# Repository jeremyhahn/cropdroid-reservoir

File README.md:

# cropdroid-reservoir

## Support

Please consider supporting this project for ongoing success and sustainability. I'm a passionate open source contributor making a professional living creating free, secure, scalable, robust, enterprise grade, distributed systems and cloud native solutions.

I'm also available for international consulting opportunities. Please let me know how I can assist you or your organization in achieving your desired security posture and technology goals.

https://github.com/sponsors/jeremyhahn

https://www.linkedin.com/in/jeremyhahn

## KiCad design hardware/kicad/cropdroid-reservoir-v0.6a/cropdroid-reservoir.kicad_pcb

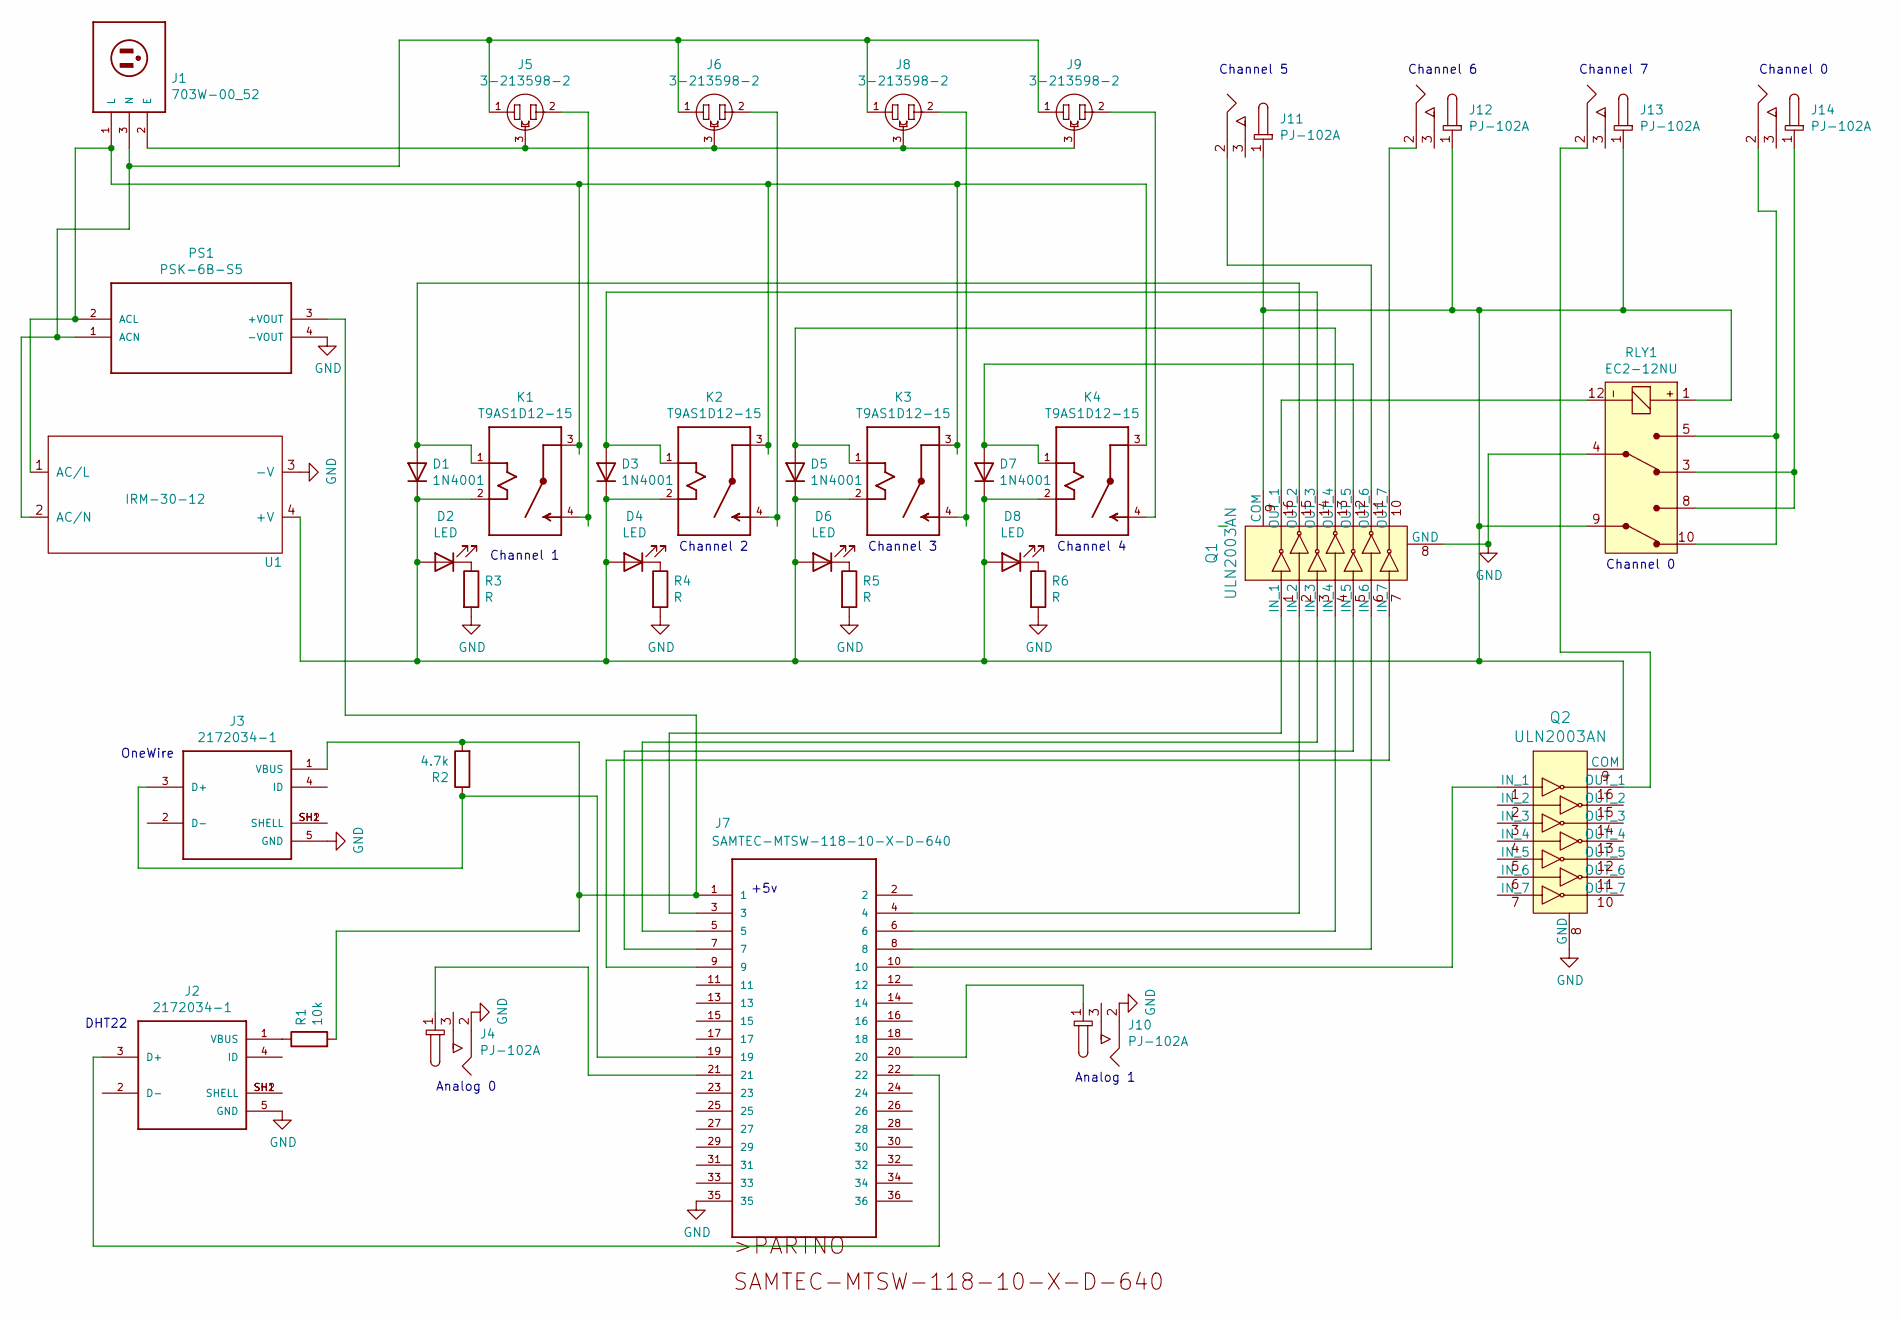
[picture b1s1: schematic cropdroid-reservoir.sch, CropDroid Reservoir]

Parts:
D1, D3, D5, D7: 1N4001; D_DO-41_SOD81_P10.16mm_Horizontal
D2, D4, D6, D8: LED; CAPPRD350W60D800H2000
J1: 703W-00_52; QUALTEK_703W-00_52
J2, J3: 2172034-1; TE_2172034-1
J4, J10, J11, J12, J13, J14: PJ-102A; Barrel_Jack_5.5mmODx2.1mmID_PJ-102A; MPN PJ-102A; Digi-Key_PN CP-102A-ND
J5, J6, J8, J9: 3-213598-2; TE_3-213598-2
J7: SAMTEC-MTSW-118-10-X-D-640
K1, K2, K3, K4: T9AS1D12-15; RELAY_T9AS1D12-15
PS1: PSK-6B-S5; CONV_PSK-6B-S5
Q1, Q2: ULN2003AN; DIP-16_W7.62mm; MPN ULN2003AN; Digi-Key_PN 296-1979-5-ND
R1: 10k; R_Axial_DIN0207_L6.3mm_D2.5mm_P10.16mm_Horizontal
R2: 4.7k; R_Axial_DIN0207_L6.3mm_D2.5mm_P10.16mm_Horizontal
R3, R4, R5, R6: R; R_Axial_DIN0207_L6.3mm_D2.5mm_P10.16mm_Horizontal
RLY1: EC2-12NU; Relay_THT_EC2; MPN EC2-12NU; Digi-Key_PN 399-11029-5-ND
U1: IRM-30-12

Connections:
GND: J2.5 (GND), J3.5 (GND), J4.2, J7.35, J10.2, PS1.4 (-VOUT), Q1.8 (GND), Q2.8 (GND), R3.2, R4.2, R5.2, R6.2, RLY1.4 (COM1), U1.3 (-V)
unnamed: D1.1 (K), D2.2 (A), D3.1 (K), D4.2 (A), D5.1 (K), D6.2 (A), D7.1 (K), D8.2 (A), J11.1, J12.1, J13.1, K1.2 (A2), K2.2 (A2), K3.2 (A2), K4.2 (A2), Q1.9 (COM), Q2.9 (COM), RLY1.1 (COIL), RLY1.9 (COM2), U1.4 (+V)
unnamed: D1.2 (A), K1.1 (A1), Q1.15 (OUT_2)
unnamed: D2.1 (K), R3.1
unnamed: D3.2 (A), K2.1 (A1), Q1.14 (OUT_3)
unnamed: D4.1 (K), R4.1
unnamed: D5.2 (A), K3.1 (A1), Q1.13 (OUT_4)
unnamed: D6.1 (K), R5.1
unnamed: D7.2 (A), K4.1 (A1), Q1.12 (OUT_5)
unnamed: D8.1 (K), R6.1
unnamed: J1.1 (L), K1.3 (C), K2.3 (C), K3.3 (C), K4.3 (C), PS1.2 (ACL), U1.1 (AC/L)
unnamed: J1.2 (E), J5.3, J6.3, J8.3, J9.3
unnamed: J1.3 (N), J5.1, J6.1, J8.1, J9.1, PS1.1 (ACN), U1.2 (AC/N)
unnamed: J2.1 (VBUS), R1.1
unnamed: J2.3 (D+), J7.22
unnamed: J2.SH1 (SHELL), J2.SH2 (SHELL)
unnamed: J3.1 (VBUS), J7.1, PS1.3 (+VOUT), R1.2, R2.2
unnamed: J3.3 (D+), J7.19, R2.1
unnamed: J3.SH1 (SHELL), J3.SH2 (SHELL)
unnamed: J4.1, J7.21
unnamed: J5.2, K1.4 (NO)
unnamed: J6.2, K2.4 (NO)
unnamed: J7.3, Q1.1 (IN_1)
unnamed: J7.4, Q1.2 (IN_2)
unnamed: J7.5, Q1.3 (IN_3)
unnamed: J7.6, Q1.4 (IN_4)
unnamed: J7.7, Q1.5 (IN_5)
unnamed: J7.8, Q1.6 (IN_6)
unnamed: J7.9, Q1.7 (IN_7)
unnamed: J7.10, Q2.1 (IN_1)
unnamed: J8.2, K3.4 (NO)
unnamed: J9.2, K4.4 (NO)
unnamed: J7.20, J10.1
unnamed: J11.2, Q1.11 (OUT_6)
unnamed: J12.2, Q1.10 (OUT_7)
unnamed: J13.2, Q2.16 (OUT_1)
unnamed: J14.1, RLY1.3 (NC1), RLY1.8 (NO2)
unnamed: J14.2, RLY1.5 (NO1), RLY1.10 (NC2)
unnamed: Q1.16 (OUT_1), RLY1.12 (COIL)

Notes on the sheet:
Channel 1
Channel 2
Channel 3
Channel 0
Channel 5
Channel 6
Channel 7
Analog 0
Analog 1
DHT22
+5v
Channel 4
OneWire

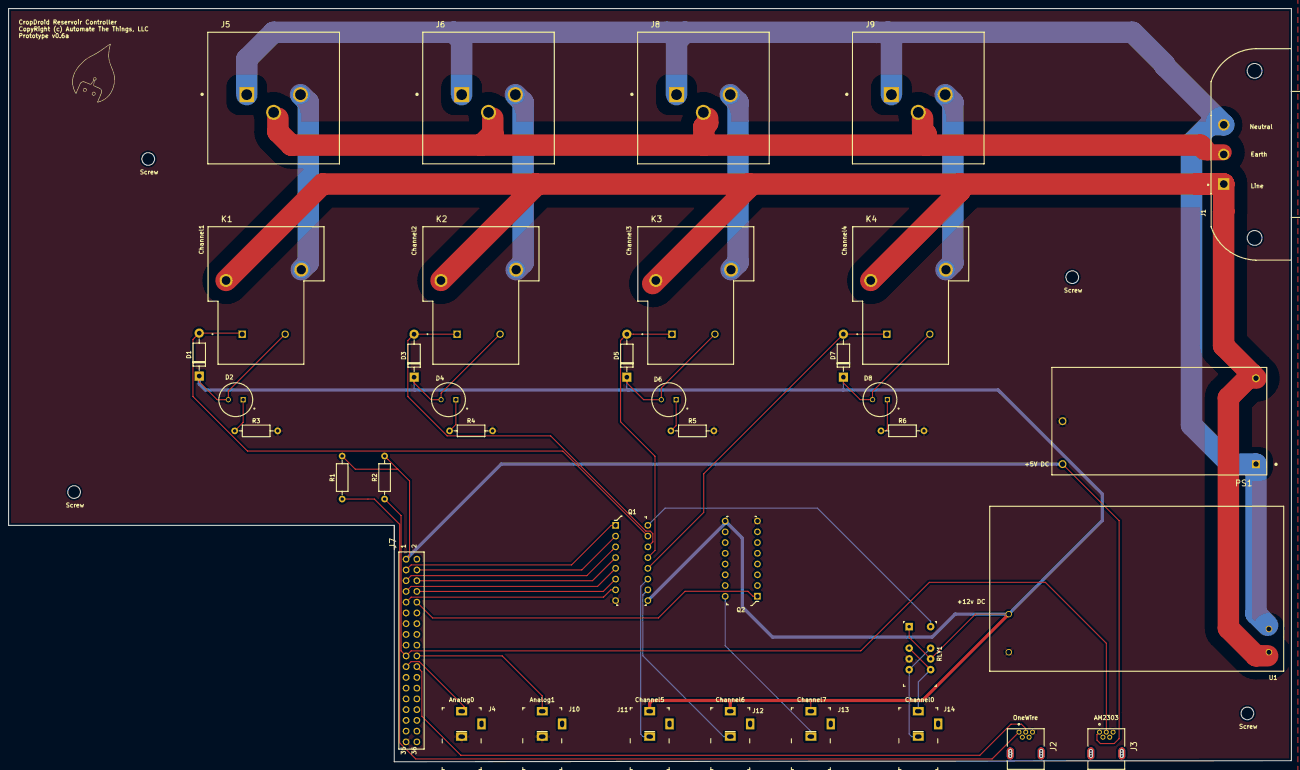
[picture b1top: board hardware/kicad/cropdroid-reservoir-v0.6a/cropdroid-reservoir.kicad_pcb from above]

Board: 2 copper layers, 303.3 x 178.1 mm, 41 parts (0 on the bottom side), 39 nets.

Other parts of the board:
Screw: Drill; Drill_Hole
Screw#2, Screw#3, Screw#4: Drill; Drill_Hole

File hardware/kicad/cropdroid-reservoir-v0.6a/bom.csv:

Reference, Quantity, Value, Footprint, Datasheet, Category, DK_Datasheet_Link, DK_Detail_Page, Description, Digi-Key_PN, Family, MPN, Manufacturer, Status, Field4, Field5, Field6
D2 D4 D6 D8 ,4,"LED","libraries:CAPPRD350W60D800H2000","~"
D3 D1 D5 D7 ,4,"1N4001","Diode_THT:D_DO-41_SOD81_P10.16mm_Horizontal","http://www.vishay.com/docs/88503/1n4001.pdf"
J1 ,1,"703W-00_52","703W-00_52:QUALTEK_703W-00_52","B","","","","","","","","","","Manufacturer Recommendations","Qualtek",""
J11 J12 J13 J14 J4 J10 ,6,"PJ-102A","digikey-footprints:Barrel_Jack_5.5mmODx2.1mmID_PJ-102A","https://www.cui.com/product/resource/digikeypdf/pj-102a.pdf","Connectors, Interconnects","https://www.cui.com/product/resource/digikeypdf/pj-102a.pdf","/product-detail/en/cui-inc/PJ-102A/CP-102A-ND/275425","CONN PWR JACK 2X5.5MM SOLDER","CP-102A-ND","Barrel - Power Connectors","PJ-102A","CUI Inc.","Active","","",""
J3 J2 ,2,"2172034-1","TE_2172034-1","Compliant","","","","","","","","","","2172034-1","https://www.te.com/usa-en/product-2172034-1.html?te_bu=Cor&t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",""
J6 J8 J5 J9 ,4,"3-213598-2","3-213598-2:TE_3-213598-2","https://www.te.com/usa-en/product-3-213598-2.html?te_bu=Cor&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","","","","","","","","","","Compliant","3-213598-2","Convenience Outlet"
J7 ,1,"SAMTEC-MTSW-118-10-X-D-640","SAMTEC-MTSW-118-10-X-D-640:SAMTEC-MTSW-118-10-X-D-640",""
K1 K2 K3 K4 ,4,"T9AS1D12-15","T9AS1D12-15:RELAY_T9AS1D12-15","https://www.te.com/usa-en/product-1-1393210-4.html?te_bu=Cor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","","","","","","","","","","1-1393210-4","",""
PS1 ,1,"PSK-6B-S5","PSK-6B-S5:CONV_PSK-6B-S5","CUI Inc","","","","","","","","","","Manufacturer recommendations","1.0",""
Q1 Q2 ,2,"ULN2003AN","digikey-footprints:DIP-16_W7.62mm","http://www.ti.com/general/docs/suppproductinfo.tsp?distId=10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","Discrete Semiconductor Products","http://www.ti.com/general/docs/suppproductinfo.tsp?distId=10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","/product-detail/en/texas-instruments/ULN2003AN/296-1979-5-ND/277624","IC PWR RELAY 7NPN 1:1 16DIP","296-1979-5-ND","Transistors - Bipolar (BJT) - Arrays","ULN2003AN","Texas Instruments","Active","","",""
R1 ,1,"10k","Resistor_THT:R_Axial_DIN0207_L6.3mm_D2.5mm_P10.16mm_Horizontal","~"
R2 ,1,"4.7k","Resistor_THT:R_Axial_DIN0207_L6.3mm_D2.5mm_P10.16mm_Horizontal","~"
R3 R4 R5 R6 ,4,"R","Resistor_THT:R_Axial_DIN0207_L6.3mm_D2.5mm_P10.16mm_Horizontal","~"
RLY1 ,1,"EC2-12NU","digikey-footprints:Relay_THT_EC2","https://api.kemet.com/component-edge/download/datasheet/EC2-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","Relays","https://api.kemet.com/component-edge/download/datasheet/EC2-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","/product-detail/en/kemet/EC2-12NU/399-11029-5-ND/4291095","RELAY GEN PURPOSE DPDT 2A 12VDC","399-11029-5-ND","Signal Relays, Up to 2 Amps","EC2-12NU","KEMET","Active","","",""
U1 ,1,"IRM-30-12","IRM-30-12:IRM-30-12",""

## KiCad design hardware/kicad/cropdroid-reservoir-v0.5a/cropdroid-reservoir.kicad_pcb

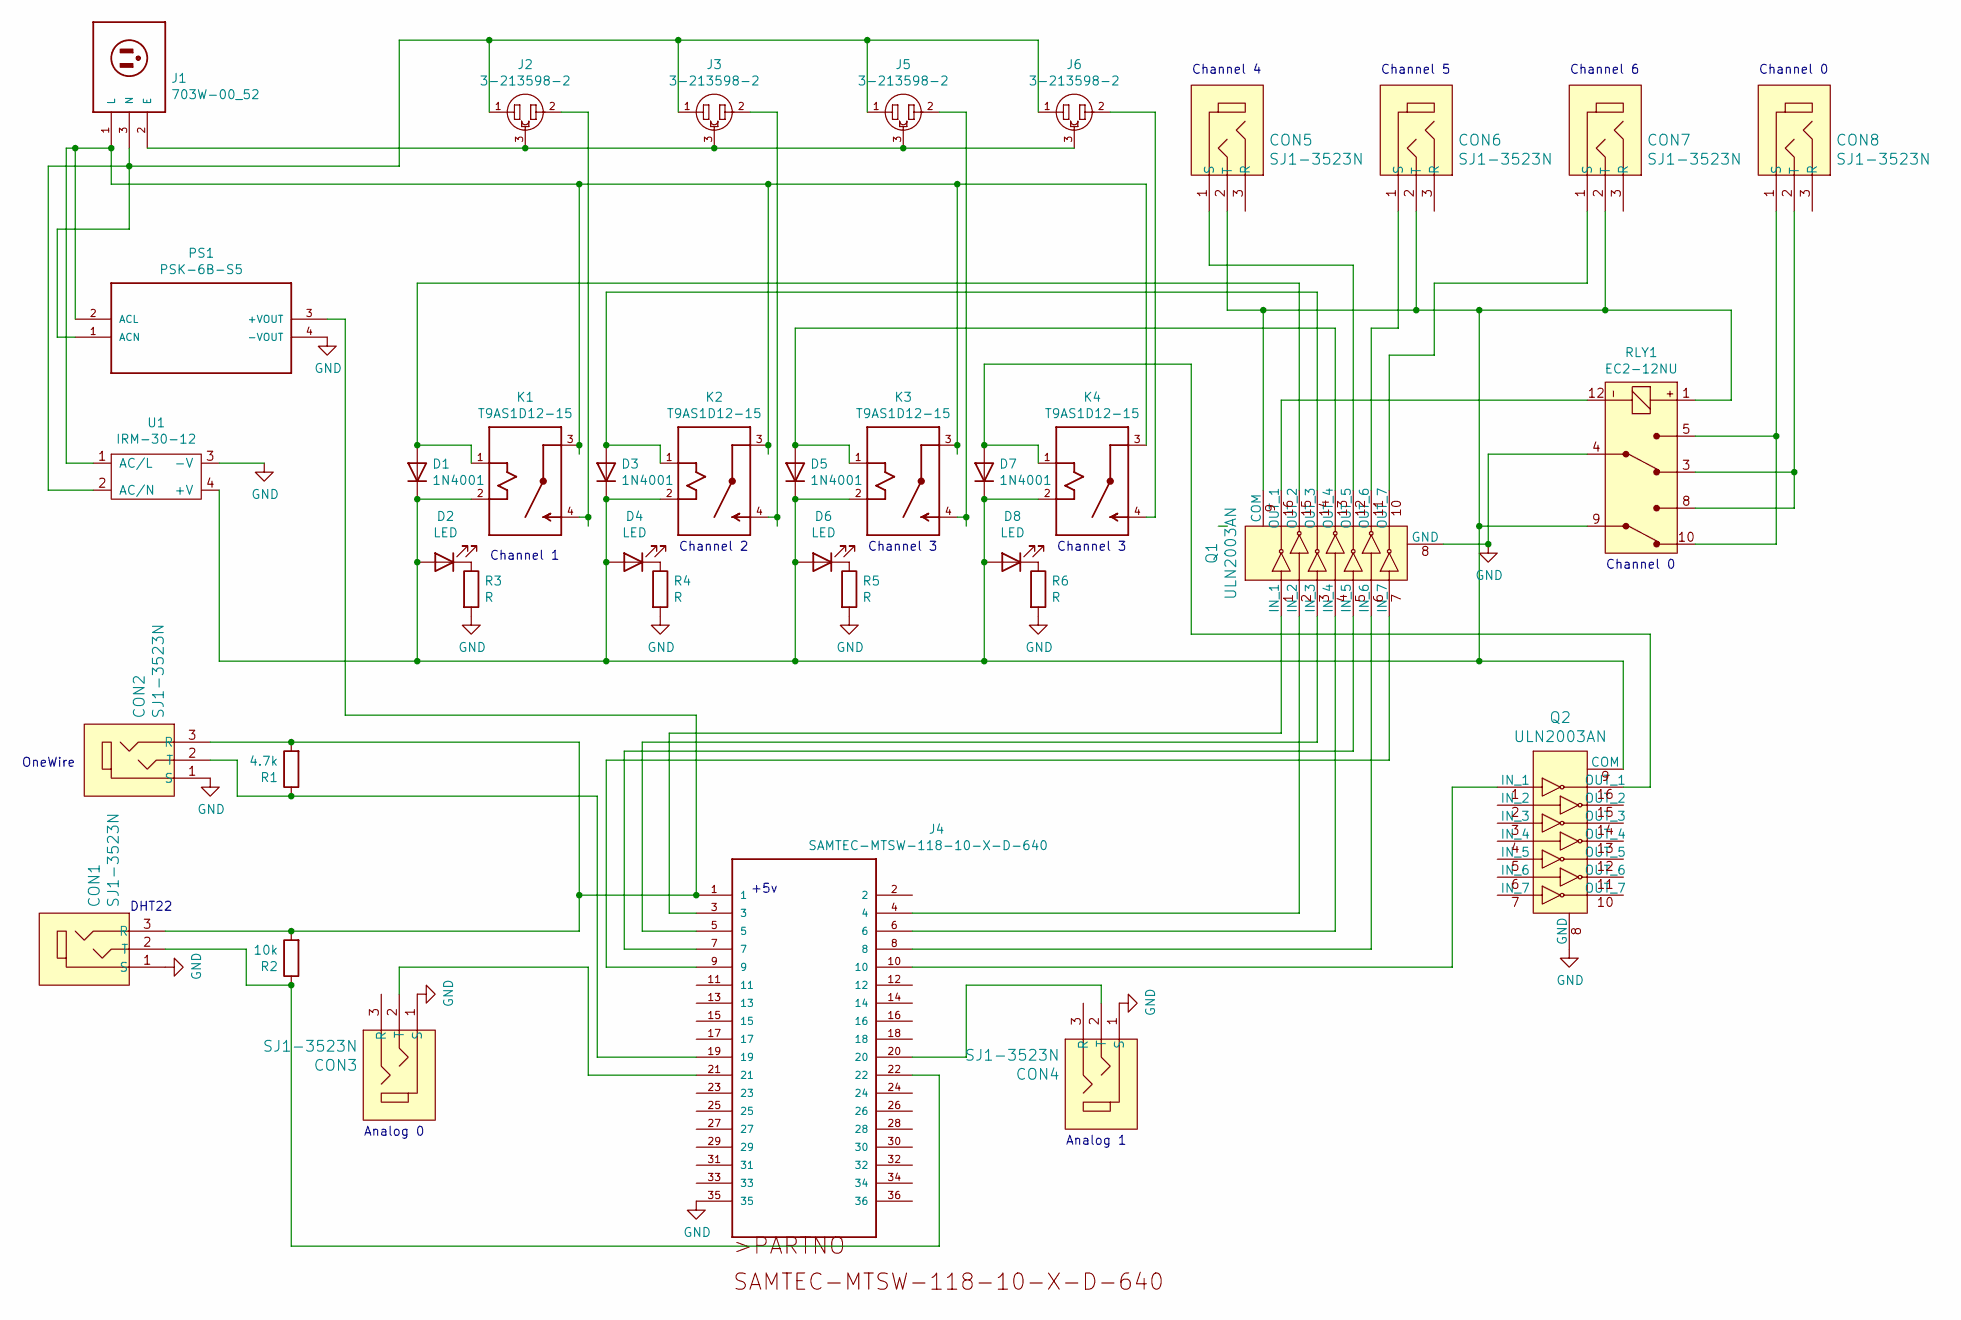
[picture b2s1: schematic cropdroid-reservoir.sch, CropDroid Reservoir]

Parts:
CON1, CON2, CON3, CON4, CON5, CON6, CON7, CON8: SJ1-3523N; Headphone_Jack_3.5mm_SJ1-3523N; MPN SJ1-3523N; Digi-Key_PN CP1-3523N-ND
D1, D3, D5, D7: 1N4001; D_DO-41_SOD81_P10.16mm_Horizontal
D2, D4, D6, D8: LED; CAPPRD350W60D800H2000
J1: 703W-00_52; QUALTEK_703W-00_52
J2, J3, J5, J6: 3-213598-2; TE_3-213598-2
J4: SAMTEC-MTSW-118-10-X-D-640
K1, K2, K3, K4: T9AS1D12-15; RELAY_T9AS1D12-15
PS1: PSK-6B-S5; CONV_PSK-6B-S5
Q1, Q2: ULN2003AN; DIP-16_W7.62mm; MPN ULN2003AN; Digi-Key_PN 296-1979-5-ND
R1: 4.7k; R_Axial_DIN0207_L6.3mm_D2.5mm_P10.16mm_Horizontal
R2: 10k; R_Axial_DIN0207_L6.3mm_D2.5mm_P10.16mm_Horizontal
R3, R4, R5, R6: R; R_Axial_DIN0207_L6.3mm_D2.5mm_P10.16mm_Horizontal
RLY1: EC2-12NU; Relay_THT_EC2; MPN EC2-12NU; Digi-Key_PN 399-11029-5-ND
U1: IRM-30-12

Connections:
GND: CON1.1 (S), CON2.1 (S), CON3.1 (S), CON4.1 (S), J4.35, PS1.4 (-VOUT), Q1.8 (GND), Q2.8 (GND), R3.2, R4.2, R5.2, R6.2, RLY1.4 (COM1), U1.3 (-V)
unnamed: CON1.2 (T), J4.22, R2.1
unnamed: CON1.3 (R), CON2.3 (R), J4.1, PS1.3 (+VOUT), R1.2, R2.2
unnamed: CON2.2 (T), J4.19, R1.1
unnamed: CON3.2 (T), J4.21
unnamed: CON4.2 (T), J4.20
unnamed: CON5.1 (S), Q1.12 (OUT_5)
unnamed: CON5.2 (T), CON6.2 (T), CON7.2 (T), D1.1 (K), D2.2 (A), D3.1 (K), D4.2 (A), D5.1 (K), D6.2 (A), D7.1 (K), D8.2 (A), K1.2 (A2), K2.2 (A2), K3.2 (A2), K4.2 (A2), Q1.9 (COM), Q2.9 (COM), RLY1.1 (COIL), RLY1.9 (COM2), U1.4 (+V)
unnamed: CON6.1 (S), Q1.11 (OUT_6)
unnamed: CON7.1 (S), Q1.10 (OUT_7)
unnamed: CON8.1 (S), RLY1.5 (NO1), RLY1.10 (NC2)
unnamed: CON8.2 (T), RLY1.3 (NC1), RLY1.8 (NO2)
unnamed: D1.2 (A), K1.1 (A1), Q1.15 (OUT_2)
unnamed: D2.1 (K), R3.1
unnamed: D3.2 (A), K2.1 (A1), Q1.14 (OUT_3)
unnamed: D4.1 (K), R4.1
unnamed: D5.2 (A), K3.1 (A1), Q1.13 (OUT_4)
unnamed: D6.1 (K), R5.1
unnamed: D7.2 (A), K4.1 (A1), Q2.16 (OUT_1)
unnamed: D8.1 (K), R6.1
unnamed: J1.1 (L), K1.3 (C), K2.3 (C), K3.3 (C), K4.3 (C), PS1.2 (ACL), U1.1 (AC/L)
unnamed: J1.2 (E), J2.3, J3.3, J5.3, J6.3
unnamed: J1.3 (N), J2.1, J3.1, J5.1, J6.1, PS1.1 (ACN), U1.2 (AC/N)
unnamed: J2.2, K1.4 (NO)
unnamed: J3.2, K2.4 (NO)
unnamed: J4.3, Q1.1 (IN_1)
unnamed: J4.4, Q1.2 (IN_2)
unnamed: J4.5, Q1.3 (IN_3)
unnamed: J4.6, Q1.4 (IN_4)
unnamed: J4.7, Q1.5 (IN_5)
unnamed: J4.8, Q1.6 (IN_6)
unnamed: J4.9, Q1.7 (IN_7)
unnamed: J4.10, Q2.1 (IN_1)
unnamed: J5.2, K3.4 (NO)
unnamed: J6.2, K4.4 (NO)
unnamed: Q1.16 (OUT_1), RLY1.12 (COIL)

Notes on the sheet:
Channel 1
Channel 2
Channel 3
Channel 0
Channel 4
Channel 5
Channel 6
Analog 0
Analog 1
OneWire
DHT22
+5v

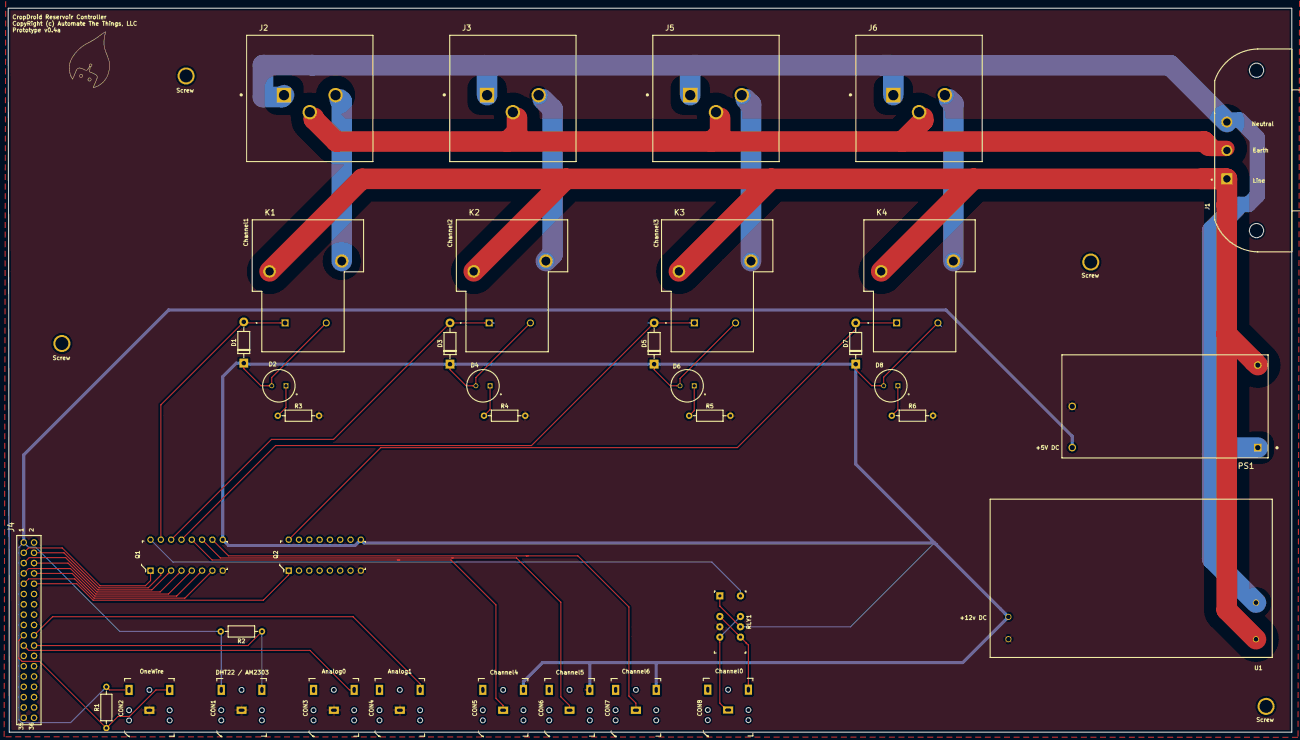
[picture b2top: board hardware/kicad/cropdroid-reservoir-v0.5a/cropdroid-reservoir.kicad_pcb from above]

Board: 2 copper layers, 316.2 x 178.4 mm, 41 parts (0 on the bottom side), 36 nets.

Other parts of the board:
Screw: Drill; Drill_Hole
Screw#2, Screw#3, Screw#4: Drill; Drill_Hole

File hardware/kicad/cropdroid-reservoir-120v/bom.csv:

Reference, Quantity, Value, Footprint, Datasheet, Category, DK_Datasheet_Link, DK_Detail_Page, Description, Digi-Key_PN, Family, MPN, Manufacturer, Status, Field4, Field5, Field6
CON7 CON8 CON6 CON5 CON3 CON2 CON4 CON1 ,8,"SJ1-3523N","digikey-footprints:Headphone_Jack_3.5mm_SJ1-3523N","https://www.cui.com/product/resource/digikeypdf/sj1-352xn_se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","Connectors, Interconnects","https://www.cui.com/product/resource/digikeypdf/sj1-352xn_se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","/product-detail/en/cui-inc/SJ1-3523N/CP1-3523N-ND/738689","CONN JACK STEREO 3.5MM R/A","CP1-3523N-ND","Barrel - Audio Connectors","SJ1-3523N","CUI Inc.","Active","","",""
D2 D4 D6 ,3,"LED","libraries:CAPPRD350W60D800H2000","~"
D3 D1 D5 ,3,"1N4001","Diode_THT:D_DO-41_SOD81_P10.16mm_Horizontal","http://www.vishay.com/docs/88503/1n4001.pdf"
J1 ,1,"703W-00_52","QUALTEK_703W-00_52","B","","","","","","","","","","Manufacturer Recommendations","Qualtek",""
J3 ,1,"SAMTEC-MTSW-118-10-X-D-640","SAMTEC-MTSW-118-10-X-D-640:SAMTEC-MTSW-118-10-X-D-640",""
J4 J5 J2 ,3,"3-213598-2","3-213598-2:TE_3-213598-2","https://www.te.com/usa-en/product-3-213598-2.html?te_bu=Cor&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","","","","","","","","","","Compliant","3-213598-2","Convenience Outlet"
K1 K2 K3 ,3,"T9AS1D12-15","T9AS1D12-15:RELAY_T9AS1D12-15","https://www.te.com/usa-en/product-1-1393210-4.html?te_bu=Cor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","","","","","","","","","","1-1393210-4","",""
PS1 ,1,"PSK-6B-S5","PSK-6B-S5:CONV_PSK-6B-S5","CUI Inc","","","","","","","","","","Manufacturer recommendations","1.0",""
Q1 ,1,"ULN2003AN","digikey-footprints:DIP-16_W7.62mm","http://www.ti.com/general/docs/suppproductinfo.tsp?distId=10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","Discrete Semiconductor Products","http://www.ti.com/general/docs/suppproductinfo.tsp?distId=10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","/product-detail/en/texas-instruments/ULN2003AN/296-1979-5-ND/277624","IC PWR RELAY 7NPN 1:1 16DIP","296-1979-5-ND","Transistors - Bipolar (BJT) - Arrays","ULN2003AN","Texas Instruments","Active","","",""
R1 ,1,"4.7k","Resistor_THT:R_Axial_DIN0207_L6.3mm_D2.5mm_P10.16mm_Horizontal","~"
R2 ,1,"10k","Resistor_THT:R_Axial_DIN0207_L6.3mm_D2.5mm_P10.16mm_Horizontal","~"
R3 R4 R5 ,3,"R","Resistor_THT:R_Axial_DIN0207_L6.3mm_D2.5mm_P10.16mm_Horizontal","~"
RLY1 ,1,"EC2-12NU","digikey-footprints:Relay_THT_EC2","https://api.kemet.com/component-edge/download/datasheet/EC2-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","Relays","https://api.kemet.com/component-edge/download/datasheet/EC2-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","/product-detail/en/kemet/EC2-12NU/399-11029-5-ND/4291095","RELAY GEN PURPOSE DPDT 2A 12VDC","399-11029-5-ND","Signal Relays, Up to 2 Amps","EC2-12NU","KEMET","Active","","",""
U1 ,1,"IRM-30-12","IRM-30-12:IRM-30-12",""

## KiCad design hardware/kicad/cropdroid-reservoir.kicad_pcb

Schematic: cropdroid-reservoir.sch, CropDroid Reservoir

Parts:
CON1, CON2, CON3, CON4, CON5, CON6, CON7: SJ1-3523N; Headphone_Jack_3.5mm_SJ1-3523N; MPN SJ1-3523N; Digi-Key_PN CP1-3523N-ND
D1, D2, D3: 1N4001; D_DO-41_SOD81_P10.16mm_Horizontal
J1, J3, J4: OSTTC020162; Term_Block_1x2_P5mm; MPN OSTTC020162; Digi-Key_PN ED2600-ND
J2: 640456-3; PinHeader_1x3_P2.54_Drill1.1mm; MPN 640456-3; Digi-Key_PN A19470-ND
J5: SAMTEC-MTSW-118-10-X-D-640
J6: PJ-102A; Barrel_Jack_5.5mmODx2.1mmID_PJ-102A; MPN PJ-102A; Digi-Key_PN CP-102A-ND
K1, K2, K3: T9AS1D12-15; RELAY_T9AS1D12-15
Q1: ULN2003AN; DIP-16_W7.62mm; MPN ULN2003AN; Digi-Key_PN 296-1979-5-ND
R3: 10k; R_Axial_DIN0207_L6.3mm_D2.5mm_P10.16mm_Horizontal
R4: 4.7k; R_Axial_DIN0207_L6.3mm_D2.5mm_P10.16mm_Horizontal
RLY1: EC2-12NU; Relay_THT_EC2; MPN EC2-12NU; Digi-Key_PN 399-11029-5-ND

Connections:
+12V: CON3.1 (S), CON5.1 (S), CON6.1 (S), D1.1 (K), D2.1 (K), D3.1 (K), J6.1, K1.2 (A2), K2.2 (A2), K3.2 (A2), Q1.9 (COM), RLY1.1 (COIL), RLY1.9 (COM2)
GND: CON1.1 (S), CON2.1 (S), CON4.1 (S), J2.3, J5.35, J6.2, Q1.8 (GND), RLY1.4 (COM1)
unnamed: CON1.2 (T), J5.21
unnamed: CON2.2 (T), J5.19, R4.1
unnamed: CON2.3 (R), J2.1, J5.1, R3.2, R4.2
unnamed: CON3.2 (T), Q1.12 (OUT_5)
unnamed: CON4.2 (T), J5.20
unnamed: CON5.2 (T), Q1.11 (OUT_6)
unnamed: CON6.2 (T), Q1.10 (OUT_7)
unnamed: CON7.1 (S), RLY1.5 (NO1), RLY1.10 (NC2)
unnamed: CON7.2 (T), RLY1.3 (NC1), RLY1.8 (NO2)
unnamed: D1.2 (A), K1.1 (A1), Q1.15 (OUT_2)
unnamed: D2.2 (A), K2.1 (A1), Q1.14 (OUT_3)
unnamed: D3.2 (A), K3.1 (A1), Q1.13 (OUT_4)
unnamed: J1.1, K1.4 (NO)
unnamed: J1.2, K1.3 (C)
unnamed: J2.2, J5.22, R3.1
unnamed: J3.1, K2.4 (NO)
unnamed: J3.2, K2.3 (C)
unnamed: J4.1, K3.4 (NO)
unnamed: J4.2, K3.3 (C)
unnamed: J5.3, Q1.1 (IN_1)
unnamed: J5.4, Q1.2 (IN_2)
unnamed: J5.5, Q1.3 (IN_3)
unnamed: J5.6, Q1.4 (IN_4)
unnamed: J5.7, Q1.5 (IN_5)
unnamed: J5.8, Q1.6 (IN_6)
unnamed: J5.9, Q1.7 (IN_7)
unnamed: Q1.16 (OUT_1), RLY1.12 (COIL)

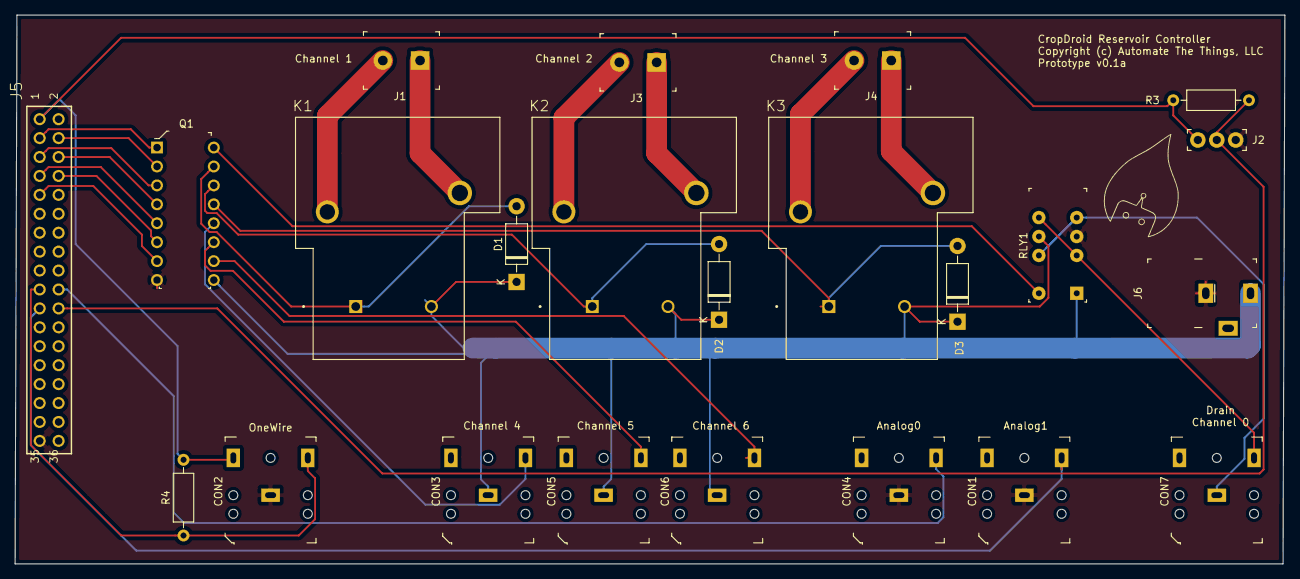
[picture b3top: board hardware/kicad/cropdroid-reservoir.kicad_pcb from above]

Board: 2 copper layers, 170.4 x 73.7 mm, 23 parts (0 on the bottom side), 29 nets.

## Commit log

2019-03-06 add initial ro solenoid logic
2019-03-10 use new default mac address
2019-04-03 remove aREST. add /reset, /reboot, /eeprom, /status endpoints
2019-04-03 fix json formatting bug
2019-04-05 change name to cropdroid-reservoir
2019-04-06 reset mac address to default. make string_buffer larger
2019-04-29 add /switch and /dispense endpoints
2019-05-07 add upper and lower float valve. refactor switch to include channel and pin
2019-05-08 fix switch channel / pin json formatting
2019-05-11 return zero instead of NaN
2019-06-12 add call to resetDefaults if macByte1 is 255
2020-02-03 add kicad project
2020-02-04 refactor kicad folder to hardware
2020-02-05 complete prototype v0.1a
2020-02-05 move logo to libraries folder
2020-02-09 add cropdroid-reservoir-120v design
2020-02-09 clean up kicad libs
2020-02-10 final kicad v0.2a
2020-02-10 final v0.3a iterations
2020-02-21 add v0.5a hardware
2020-02-21 v0.5a final
2020-02-21 remove xml bom
2020-03-01 v0.6a hardware
2020-03-01 fix broken board edge
2020-03-01 add board dimension drawings. space dc power jacks 3/4 in apart
2020-03-02 rename gerber folder to plots, generate final v0.6a artifacts for fab shop
2020-03-11 add /sys endpoint
2020-04-13 return metrics as array. fix /reboot and /reset, rename /dispense to /timer
2020-04-13 return metrics as array instead of array of objects
2020-04-17 rename uppercase metrics to lowercapse (API)
2021-07-27 move float pins to A14 and A15 to avoid conflict w/ ethernet. fix memory leak and channel size bug
2021-09-18 bump hardware res-v0.1b and firmware v1.0.0b
2024-01-16 Add Makefile firmware download target. Add hardware image to README
2024-01-16 Crop hardware image
2024-01-16 Add hardware flow image
2024-07-07 Add Fusion 360 images and source files

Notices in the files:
hardware/kicad/cropdroid-reservoir-120v/cropdroid-reservoir.sch:
License: Proprietary
hardware/kicad/cropdroid-reservoir-v0.5a/cropdroid-reservoir.kicad_pcb:
CopyRight (c) Automate The Things, LLC
